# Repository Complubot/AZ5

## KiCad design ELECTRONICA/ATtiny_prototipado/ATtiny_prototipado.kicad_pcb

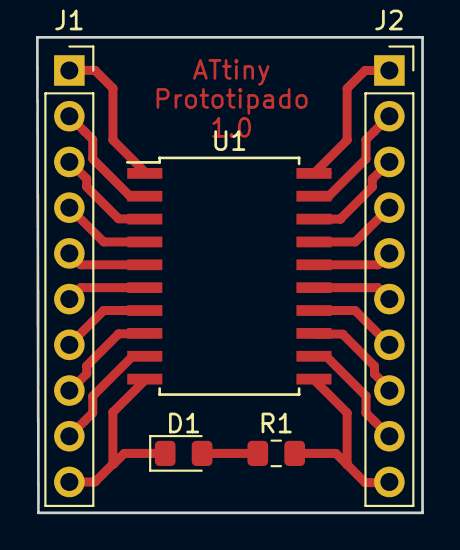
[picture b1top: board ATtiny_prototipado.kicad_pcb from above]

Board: 2 copper layers, 21.4 x 26.4 mm, 5 parts (0 on the bottom side), 21 nets.

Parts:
D1: LED; LED_0805_2012Metric_Pad1.15x1.40mm_HandSolder
J1: Conector_izquierdo; PinSocket_1x10_P2.54mm_Vertical
J2: Conector_derecho; PinSocket_1x10_P2.54mm_Vertical
R1: R; R_0805_2012Metric_Pad1.15x1.40mm_HandSolder
U1: ATtiny1634-SU; SOIC-20W_7.5x12.8mm_P1.27mm

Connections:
Earth: D1.1, J1.10, U1.10
unnamed: D1.2, R1.1
PA0: J1.9, U1.9
PA1: J1.8, U1.8
PA2: J1.7, U1.7
PA3: J1.6, U1.6
PA4: J1.5, U1.5
PA5: J1.4, U1.4
PA6: J1.3, U1.3
PA7: J1.2, U1.2
PB0: J1.1, U1.1
PB1: J2.1, U1.20
PB2: J2.2, U1.19
PB3: J2.3, U1.18
PC0: J2.4, U1.17
PC1: J2.5, U1.16
PC2: J2.6, U1.15
PC3: J2.7, U1.14
PC4: J2.8, U1.13
PC5: J2.9, U1.12
VCC: J2.10, R1.2, U1.11

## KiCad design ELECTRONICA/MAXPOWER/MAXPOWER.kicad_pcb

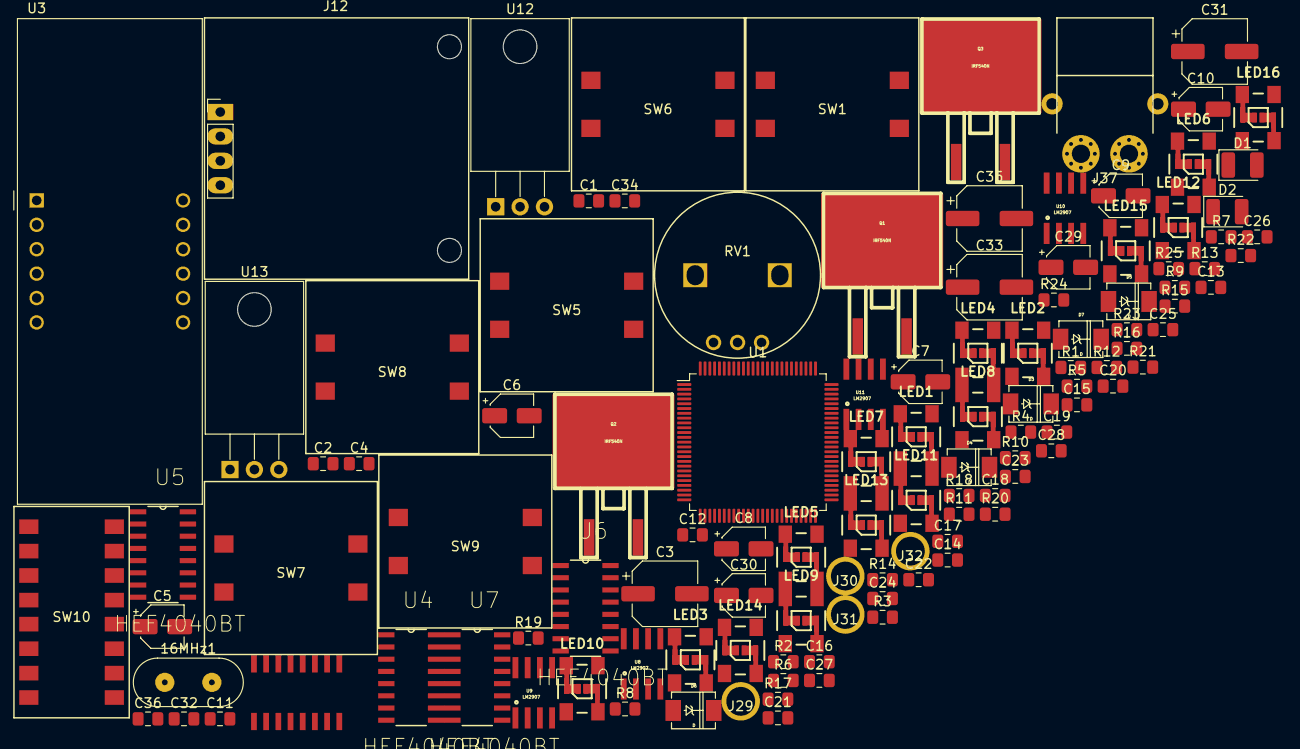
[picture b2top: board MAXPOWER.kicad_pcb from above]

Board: 2 copper layers, 115 parts (0 on the bottom side), 87 nets, no tracks yet.

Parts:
16MHz1: Crystal
C1, C2: 22pF; C_0805_2012Metric_Pad1.15x1.40mm_HandSolder
C3, C31, C33, C35: e47uF; CP_Elec_6.3x5.3
C4, C11, C13, C14, C15, C16, C17, C18, C19, C20, C21, C22, C23, C24, C25, C26, C27, C28, C32, C34, C36: 100nF; C_0805_2012Metric_Pad1.15x1.40mm_HandSolder
C5, C6, C7, C8: e100nF; CP_Elec_4x5.3
C9, C10, C29, C30: e1uF; CP_Elec_4x5.3
C12: 220nF; C_0805_2012Metric_Pad1.15x1.40mm_HandSolder
D1, D2: LED; LED_1210_3225Metric_Pad1.42x2.65mm_HandSolder
D3, D4, D5, D6, D7: D; DO-214AA
J12: Conn_01x04_OLED; OLED
J29: HOLE1; hole
J30: HOLE2; hole
J31: HOLE3; hole
J32: HOLE4; hole
J37: Conn_01x02_INPUT; XT30PW-F2
LED1, LED2, LED3, LED4, LED5, LED6, LED7, LED8, LED9, LED10, LED11, LED12, LED13, LED14, LED15, LED16: WS2812B; WS2812B_data-bridgeable
Q1, Q2, Q3: IRF540N; D2PAK
R1, R16: 249; R_0805_2012Metric_Pad1.15x1.40mm_HandSolder
R2, R3, R4, R5, R9, R10, R12, R14, R25: 10K; R_0805_2012Metric_Pad1.15x1.40mm_HandSolder
R6: 2K; R_0805_2012Metric_Pad1.15x1.40mm_HandSolder
R7, R11, R13, R15, R21, R22, R23, R24: 1K; R_0805_2012Metric_Pad1.15x1.40mm_HandSolder
R8: 10k; R_0805_2012Metric_Pad1.15x1.40mm_HandSolder
R17, R18, R19, R20: 11,3K; R_0805_2012Metric_Pad1.15x1.40mm_HandSolder
RV1: R_POT; Potenciometro
SW1: RESET; PULSADOR
SW5: UP; PULSADOR
SW6: RIGHT; PULSADOR
SW7: LEFT; PULSADOR
SW8: OK; PULSADOR
SW9: DOWN; PULSADOR
SW10: SW_DIP_x08; SWITCH
U1: ATmega2560-16AU; TQFP-100_14x14mm_P0.5mm
U2: 74LS247; SO16
U3: CC56-12SYKWA; CA56-12SYKWA
U4, U5, U6, U7: HEF4040BT; SOIC127P600X175-16N
U8, U9, U10, U11: LM2907; SOIC8
U12, U13: L7805; 7805

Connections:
+5V: C33.1, C34.2, D1.2, J12.3, R3.1, R4.1, R5.1, R8.1, R9.1, RV1.1, U2.3, U2.5, U2.16, U4.16, U5.16, U6.16, U7.16
+5VL: C3.1, C4.2, C11.1, C14.1, C15.1, C16.1, C17.1, C18.1, C19.1, C20.1, C21.1, C22.1, C23.1, C24.1, C25.1, C26.1, C27.1, C28.1, LED1.1, LED2.1, LED3.1, LED4.1, LED5.1, LED6.1, LED7.1, LED8.1, LED9.1, LED10.1, LED11.1, LED12.1, LED13.1, LED14.1, LED15.1, LED16.1
+5VP: C31.1, C32.2, R25.1, U1.10, U1.31, U1.61, U1.80, U1.100
+12V: C35.1, C36.2, U8.5, U8.6, U9.5, U9.6, U10.5, U10.6, U11.5, U11.6
B_LED: R11.1, U1.24
CLK1: 16MHz1.1, C1.1, U1.34
CLK2: 16MHz1.2, C2.2, U1.33
DISPLAY_1: U1.57, U3.12
DISPLAY_2: U1.58, U3.9
DISPLAY_3: U1.59, U3.8
DISPLAY_4: U1.60, U3.6
DISPLAY_A: U1.53, U2.7
DISPLAY_B: U1.54, U2.1
DISPLAY_C: U1.55, U2.2
DISPLAY_D: U1.56, U2.6
DOWN: SW9.2, U1.39
EN1: R23.2, U1.93, U10.4, U10.7
EN2: R24.2, U1.92, U11.4, U11.7
EN3: R21.2, U1.91, U8.4, U8.7
EN4: R22.2, U1.90, U9.4, U9.7
EN_IN4: U6.10, U7.10
EN_T1: U4.4, U10.1
EN_T2: U5.4, U11.1
EN_T3: U6.4, U8.1
EN_T4: U7.4, U9.1
Earth: C1.2, C2.1, C3.2, C4.1, C5.2, C6.2, C7.2, C8.2, C9.2, C10.2, C11.2, C13.2, C14.2, C15.2, C16.2, C17.2, C18.2, C19.2, C20.2, C21.2, C22.2, C23.2, C24.2, C25.2, C26.2, C27.2, C28.2, C29.2, C30.2, C31.2, C32.1, C33.2, C34.1, C35.2, C36.1, D2.1, J12.4, J37.2, LED1.3, LED2.3, LED3.3, LED4.3, LED5.3, LED6.3, LED7.3, LED8.3, LED9.3, LED10.3, LED11.3, LED12.3, LED13.3, LED14.3, LED15.3, LED16.3, R1.1, R2.2, R6.1, R17.2, R18.2, R19.2, R20.2, R21.1, R22.1, R23.1, R24.1, RV1.3, SW1.2, SW5.1, SW6.1, SW7.1, SW8.1, SW9.1, SW10.1, SW10.2, SW10.3, SW10.4, SW10.5, SW10.6, SW10.7, SW10.8, U1.11, U1.32, U1.62, U1.81, U1.99, U2.8, U4.8, U4.11, U5.8, U5.11, U6.8, U6.11, U7.8, U7.11, U8.8, U9.8, U10.8, U11.8
FAST_LED: LED1.4, U1.25
G_LED: R13.1, U1.23
LEFT: SW7.2, U1.37
unnamed: C5.1, U8.2
unnamed: C6.1, U9.2
unnamed: C7.1, U10.2
unnamed: C8.1, U11.2
unnamed: C9.1, R17.1, U8.3
unnamed: C10.1, R18.1, U9.3
unnamed: C12.1, C13.1, R25.2, SW1.1, U1.30
unnamed: C29.1, R19.1, U10.3
unnamed: C30.1, R20.1, U11.3
unnamed: D1.1, R1.2
unnamed: D2.2, R16.1
unnamed: D4.1, D6.1
unnamed: R6.2, R7.2
unnamed: LED1.2, LED2.4
unnamed: LED2.2, LED3.4
unnamed: LED3.2, LED4.4
unnamed: LED4.2, LED5.4
unnamed: LED5.2, LED6.4
unnamed: LED6.2, LED7.4
unnamed: LED7.2, LED8.4
unnamed: LED10.2, LED11.4
unnamed: LED9.2, LED10.4
unnamed: LED11.2, LED12.4
unnamed: LED12.2, LED13.4
unnamed: LED13.2, LED14.4
unnamed: LED14.2, LED15.4
unnamed: LED15.2, LED16.4
unnamed: R10.1, R11.2
unnamed: R12.1, R13.2
unnamed: R14.1, R15.2
unnamed: R16.2, U1.26
unnamed: SW10.9, U1.79
unnamed: SW10.10, U1.69
unnamed: SW10.11, U1.68
unnamed: SW10.12, U1.67
unnamed: SW10.13, U1.66
unnamed: SW10.14, U1.65
unnamed: SW10.15, U1.64
unnamed: SW10.16, U1.63
unnamed: U2.4, U3.3
unnamed: U2.9, U3.1
unnamed: U2.10, U3.2
unnamed: U2.11, U3.4
unnamed: U2.12, U3.7
unnamed: U2.13, U3.11
unnamed: U2.14, U3.5
unnamed: U2.15, U3.10
OK: SW8.2, U1.38
POT: RV1.2, U1.89
RESET_Bluetooth: R2.1, R3.2
RIGHT: SW6.2, U1.36
RX0: R7.1, U1.2, U1.12
R_LED: R15.1, U1.1
SCL: J12.2, R8.2, U1.43
SDA: J12.1, R9.2, U1.44
TX0: U1.3, U1.13
UP: SW5.2, U1.35
VCC: D3.2, D4.2, D5.2, D6.2, D7.2, J37.1

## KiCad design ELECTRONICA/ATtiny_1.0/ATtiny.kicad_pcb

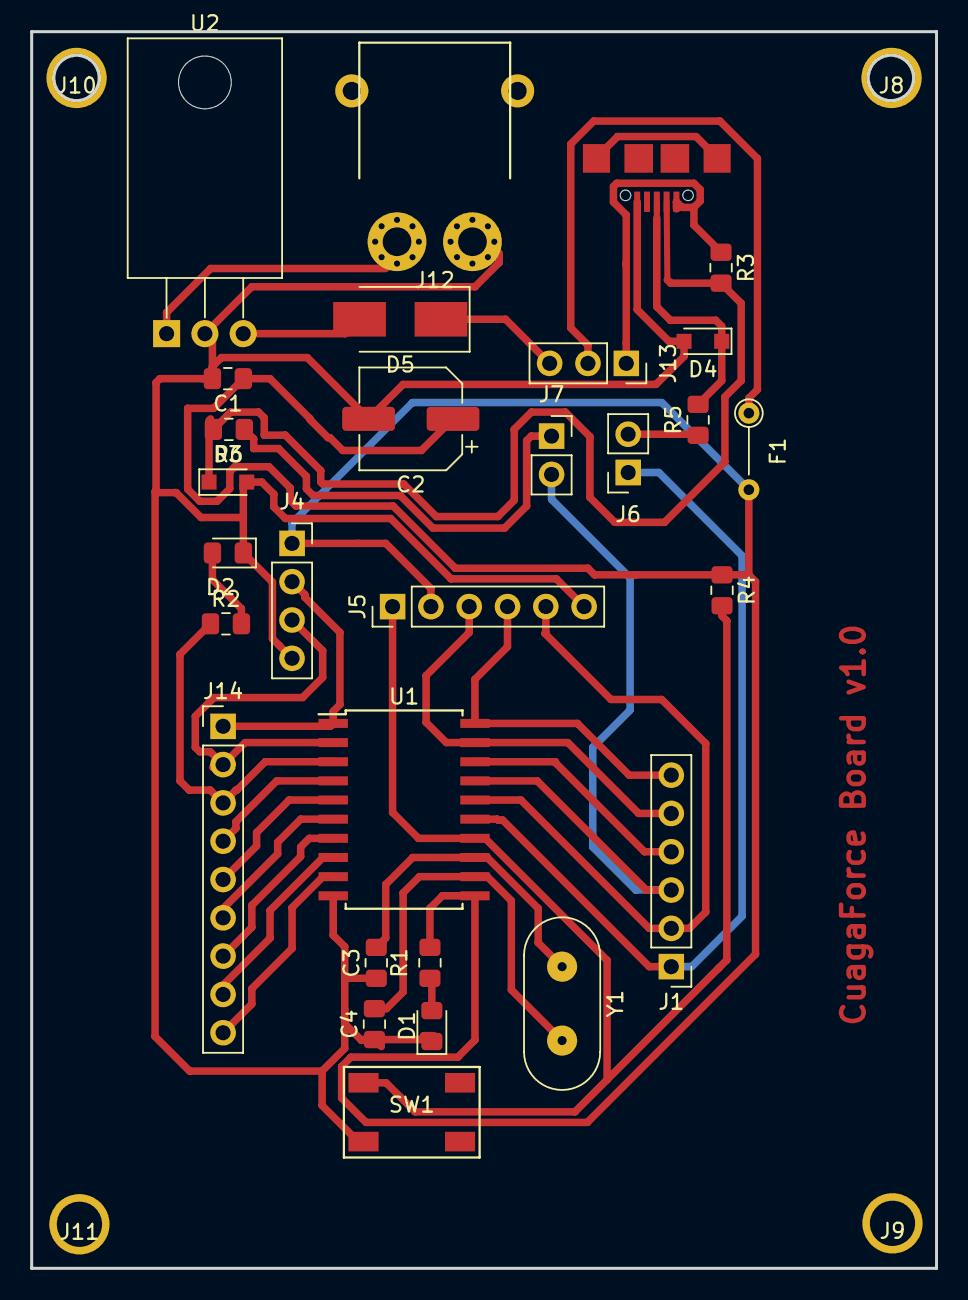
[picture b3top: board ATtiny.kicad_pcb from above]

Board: 2 copper layers, 60.0 x 82.0 mm, 33 parts (0 on the bottom side), 31 nets.

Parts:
C1: C100nF; C_0805_2012Metric_Pad1.15x1.40mm_HandSolder
C2: CP47uF; CP_Elec_6.3x5.3
C3, C4: C22pF; C_0805_2012Metric_Pad1.15x1.40mm_HandSolder
D1, D2: LED; LED_0805_2012Metric_Pad1.15x1.40mm_HandSolder
D3, D4: D_Zener; D_SOD-323_HandSoldering
D5: US2D; D_SMB_Handsoldering
F1: Polyfuse; R_Axial_DIN0204_L3.6mm_D1.6mm_P5.08mm_Vertical
J1: Conn_01x06; PinHeader_1x06_P2.54mm_Vertical
J2: USB_B_Micro; MICRO_USB_SMD
J4: Conn_01x04_Serie_0; PinSocket_1x04_P2.54mm_Vertical
J5: Conn_01x06_Serie_1_ICSP; PinHeader_1x06_P2.54mm_Vertical
J6, J7: Conn_01x02; PinSocket_1x02_P2.54mm_Vertical
J8, J9, J10, J11: Agujero; hole
J12: Conn_01x02_XT30; XT30PW-F
J13: Conn_01x03_Alimentacion; PinSocket_1x03_P2.54mm_Vertical
J14: Conn_01x09; PinHeader_1x09_P2.54mm_Vertical
R1, R2: R330; R_0805_2012Metric_Pad1.15x1.40mm_HandSolder
R3, R4: R10K; R_0805_2012Metric_Pad1.15x1.40mm_HandSolder
R5, R6: R68; R_0805_2012Metric_Pad1.15x1.40mm_HandSolder
SW1: SW_Push; Pulsador_5,2x5,2
U1: ATtiny1634-SU; SOIC-20W_7.5x12.8mm_P1.27mm
U2: L7805; 7805
Y1: Crystal 16MHz; Crystal

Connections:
+5V: C1.1, C2.1, F1.2, J4.1, J5.2, R1.2, R4.1, U1.11
D+: J1.1, J6.1, U1.15
D-: J1.3, J7.2, U1.17
Earth: C1.2, C2.2, C3.1, C4.1, D1.1, D2.1, D3.2, D4.2, J2.5, J4.4, J5.6, J12.1, SW1.2, U1.10, U2.2
MISO: J1.5, J5.3, U1.19
MOSI: J1.6, J5.4, U1.20
unnamed: C3.2, U1.13, Y1.1
unnamed: C4.2, U1.12, Y1.2
unnamed: D1.2, R1.1
unnamed: D2.2, R2.2
unnamed: D3.1, J2.2, R3.2, R6.2
unnamed: D4.1, J2.3, R5.2
unnamed: D5.1, J13.3
unnamed: D5.2, U2.3
unnamed: F1.1, J13.2
unnamed: J6.2, R5.1
unnamed: J7.1, R6.1
PA0: J14.9, U1.9
PA1: J14.8, U1.8
PA2: J14.7, U1.7
PA3: J14.6, U1.6
PA4: J14.5, U1.5
PA5: J14.4, U1.4
PA6: J14.3, R2.1, U1.3
PB3: J1.4, U1.18
RESET: J5.1, R4.2, SW1.1, U1.14
RX0: J4.3, J14.2, U1.2
SCK: J1.2, J5.5, U1.16
TX0: J4.2, J14.1, U1.1
VCC: J2.1, J13.1, R3.1
VPP: J12.2, U2.1

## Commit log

2018-12-03 miscelaneous
2018-12-03 elec
2018-12-28 diseños de mecánica (MOTOR/PERFIL/PLANTA/POLEAS/RUEDA) --falta la escuadra de los motores
2018-12-28 mecanica design (planta con perfiles/ escuadra añadida a motor y a conjunto)
2018-12-28 tamaño de la L aumentado para cubrir al motor
2018-12-28 pedestal añadido en sistema motriz
2018-12-28 codigo arduino para probar la comunicacion serial con un programa en cpp
2018-12-28 ubuntu.md
2019-01-03 ros_package
2019-01-03 ros_pub_sub
2019-01-03 .srv and .msg in client_server
2019-01-03 server_client
2019-01-04 Esquema electrico
2019-01-04 raylib
2019-01-04 kicad
2019-01-14 MOTOR MADERA
2019-01-18 kicad pines de expansion
2019-01-18 kicad motor encoders
2019-01-23 kicad opencv
2019-01-25 opencv
2019-01-25 line detector test
2019-01-28 solid edge
2019-01-28 gitmodules
2019-01-28 windows
2019-01-28 nuevo motor maderaq
2019-01-28 con.kicad_mod
2019-01-28 Rename DRILL_32.kicad_mod to DRILL__32.kicad_mod
2019-01-28 rm conn
2019-02-01 MOTOR
2019-02-01 motor_lib
2019-02-01 motor_madera
2019-02-02 new motor system
2019-02-04 placa ATtiny1634
2019-02-04 kicad attinny
2019-02-04 libraries
2019-02-04 version estable kicad
2019-02-25 attiny interrupt
2019-03-01 libreria attiny: interrupciones y pwm
2019-03-02 no se lo que hago hulio
2019-03-08 millis, nanos y encoder
2019-03-25 Serial
2019-04-01 Complubot
2019-04-01 attyni
2019-04-12 Desarrollo de la Tiny 2.0
2019-04-22 impresiontinny
2019-04-22 plantilla tinny
2019-05-27 27-5-2019
2019-06-04 4-6-19
2019-06-04 ultrasound
2019-06-04 updated flask
2019-06-08 controller web ui
2019-06-10 controller reader and controller tanformer to pollotron robot
2019-06-12 us design and base (mecanic)
2019-06-14 pollotron ros
2019-06-14 controller
2019-07-01 1-June-2019
2019-07-01 intel realsense
2019-07-15 Desarrollo de los sitemas de visión en ROS, lectura de los encoders de los motores y comunicación por I2C de las placas ATTiny, e inicio de la tercera revisión del diseño de las mismas
2019-09-25 odom
2019-09-28 cmd_vel
2020-01-17 slam
2020-01-27 gitignore
2020-01-27 person tracker
2020-01-27 rename
2021-04-07 Bump bottle from 0.12.13 to 0.12.19 in /WEB/arduino
    Bumps [bottle](https://github.com/bottlepy/bottle) from 0.12.13 to 0.12.19.
    - [Release notes](https://github.com/bottlepy/bottle/releases)
    - [Changelog](https://github.com/bottlepy/bottle/blob/master/docs/changelog.rst)
    - [Commits](https://github.com/bottlepy/bottle/compare/0.12.13...0.12.19)
2022-06-03 Bump bottle from 0.12.13 to 0.12.20 in /WEB/arduino
    Bumps [bottle](https://github.com/bottlepy/bottle) from 0.12.13 to 0.12.20.
    - [Release notes](https://github.com/bottlepy/bottle/releases)
    - [Changelog](https://github.com/bottlepy/bottle/blob/master/docs/changelog.rst)
    - [Commits](https://github.com/bottlepy/bottle/compare/0.12.13...0.12.20)
    ---
    updated-dependencies:
2023-07-20 Bump bottle from 0.12.13 to 0.12.20 in /WEB/webpage
    Bumps [bottle](https://github.com/bottlepy/bottle) from 0.12.13 to 0.12.20.
    - [Changelog](https://github.com/bottlepy/bottle/blob/master/docs/changelog.rst)
    - [Commits](https://github.com/bottlepy/bottle/compare/0.12.13...0.12.20)
    ---
    updated-dependencies:
    - dependency-name: bottle
